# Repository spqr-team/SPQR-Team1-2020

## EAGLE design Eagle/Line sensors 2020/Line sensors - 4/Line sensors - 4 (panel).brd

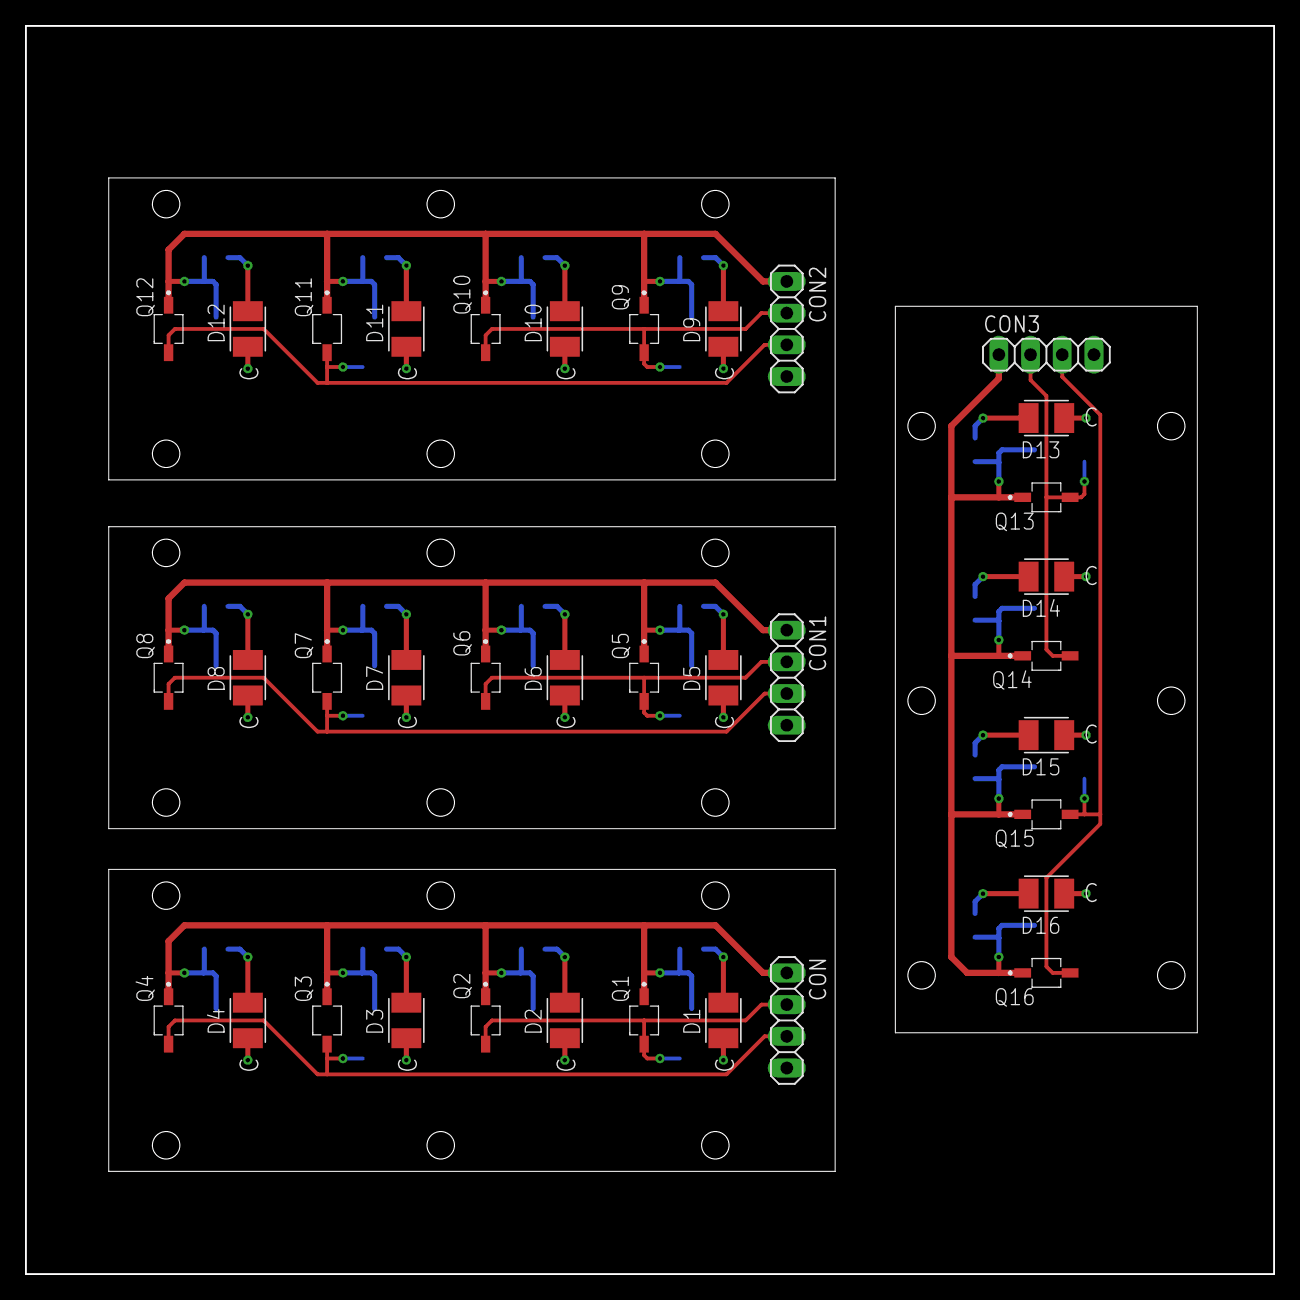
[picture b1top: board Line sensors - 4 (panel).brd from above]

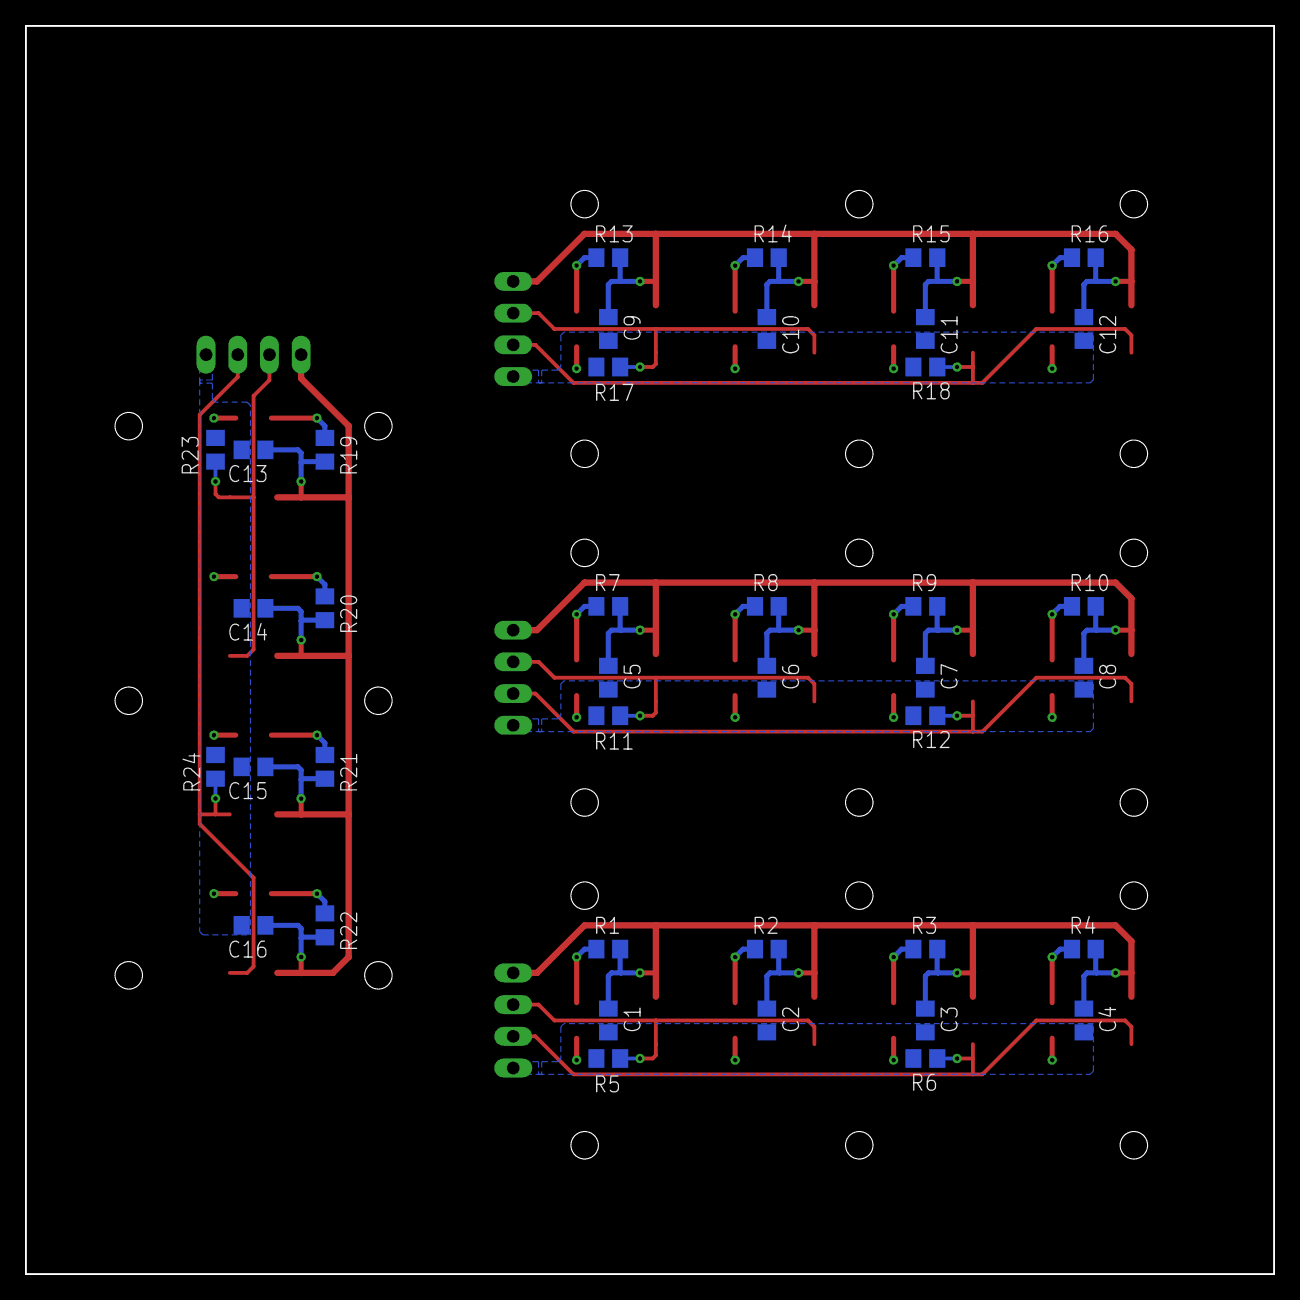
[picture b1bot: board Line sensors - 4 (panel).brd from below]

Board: 2 copper layers, 100.0 x 100.0 mm, 76 parts (40 on the bottom side), 32 nets.

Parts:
C1, C2, C3, C4, C5, C6, C7, C8, C9, C10, C11, C12, C13, C14, C15, C16: C0805
CON, CON1, CON2, CON3: 1X04
D1, D2, D3, D4, D5, D6, D7, D8, D9, D10, D11, D12, D13, D14, D15, D16: 3528-2PIN
Q1, Q2, Q3, Q4, Q5, Q6, Q7, Q8, Q9, Q10, Q11, Q12, Q13, Q14, Q15, Q16: VEMT2520X01
R1, R2, R3, R4, R5, R6, R7, R8, R9, R10, R11, R12, R13, R14, R15, R16, R17, R18, R19, R20, R21, R22, R23, R24: R0805

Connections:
GND: C1.2, C2.2, C3.2, C4.2, CON.4, D1.1, D2.1, D3.1, D4.1, R5.1, R6.1
GND1: C5.2, C6.2, C7.2, C8.2, CON1.4, D5.1, D6.1, D7.1, D8.1, R11.1, R12.1
GND2: C9.2, C10.2, C11.2, C12.2, CON2.4, D9.1, D10.1, D11.1, D12.1, R17.1, R18.1
GND3: C13.2, C14.2, C15.2, C16.2, CON3.4, D13.1, D14.1, D15.1, D16.1, R23.1, R24.1
unnamed: D1.2, R1.1
unnamed: D2.2, R2.1
unnamed: D3.2, R3.1
unnamed: D4.2, R4.1
unnamed: D5.2, R7.1
unnamed: D6.2, R8.1
unnamed: D7.2, R9.1
unnamed: D8.2, R10.1
unnamed: D9.2, R13.1
unnamed: D10.2, R14.1
unnamed: D11.2, R15.1
unnamed: D12.2, R16.1
unnamed: D13.2, R19.1
unnamed: D14.2, R20.1
unnamed: D15.2, R21.1
unnamed: D16.2, R22.1
SIG1: CON.2, Q1.2, Q2.2, R5.2
SIG2: CON.3, Q3.2, Q4.2, R6.2
SIG3: CON1.2, Q5.2, Q6.2, R11.2
SIG4: CON1.3, Q7.2, Q8.2, R12.2
SIG5: CON2.2, Q9.2, Q10.2, R17.2
SIG6: CON2.3, Q11.2, Q12.2, R18.2
SIG7: CON3.2, Q13.2, Q14.2, R23.2
SIG8: CON3.3, Q15.2, Q16.2, R24.2
V+: C1.1, C2.1, C3.1, C4.1, CON.1, Q1.1, Q2.1, Q3.1, Q4.1, R1.2, R2.2, R3.2, R4.2
V+1: C5.1, C6.1, C7.1, C8.1, CON1.1, Q5.1, Q6.1, Q7.1, Q8.1, R7.2, R8.2, R9.2, R10.2
V+2: C9.1, C10.1, C11.1, C12.1, CON2.1, Q9.1, Q10.1, Q11.1, Q12.1, R13.2, R14.2, R15.2, R16.2
V+3: C13.1, C14.1, C15.1, C16.1, CON3.1, Q13.1, Q14.1, Q15.1, Q16.1, R19.2, R20.2, R21.2, R22.2

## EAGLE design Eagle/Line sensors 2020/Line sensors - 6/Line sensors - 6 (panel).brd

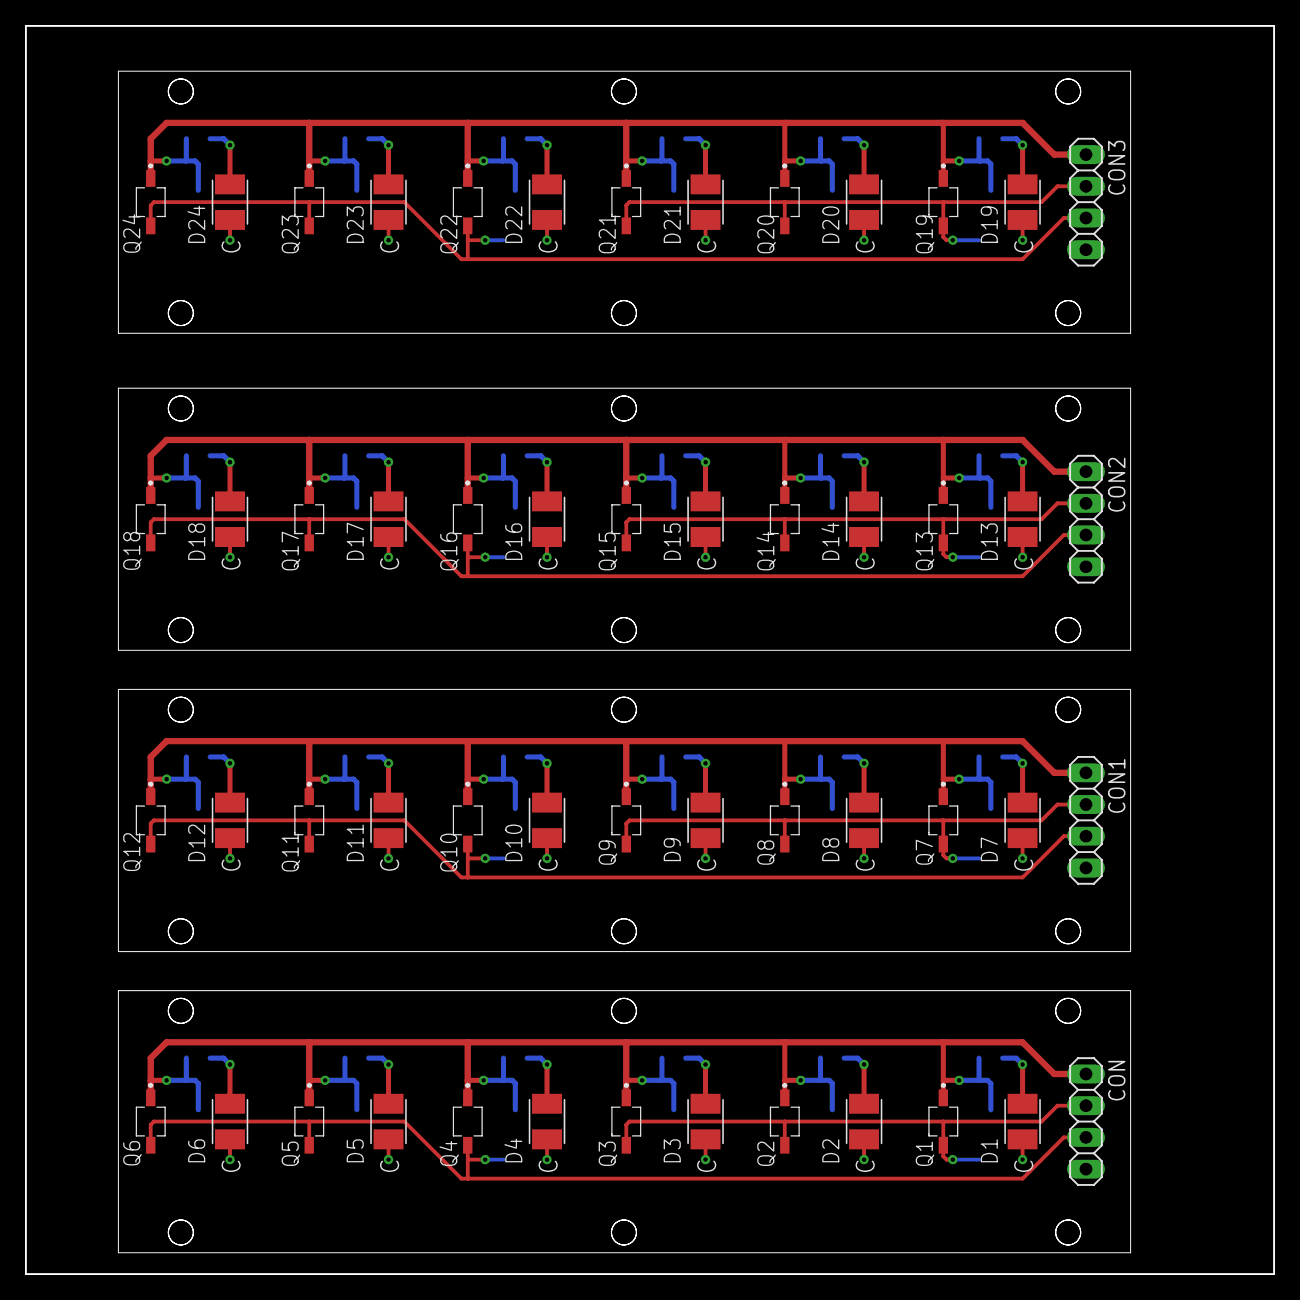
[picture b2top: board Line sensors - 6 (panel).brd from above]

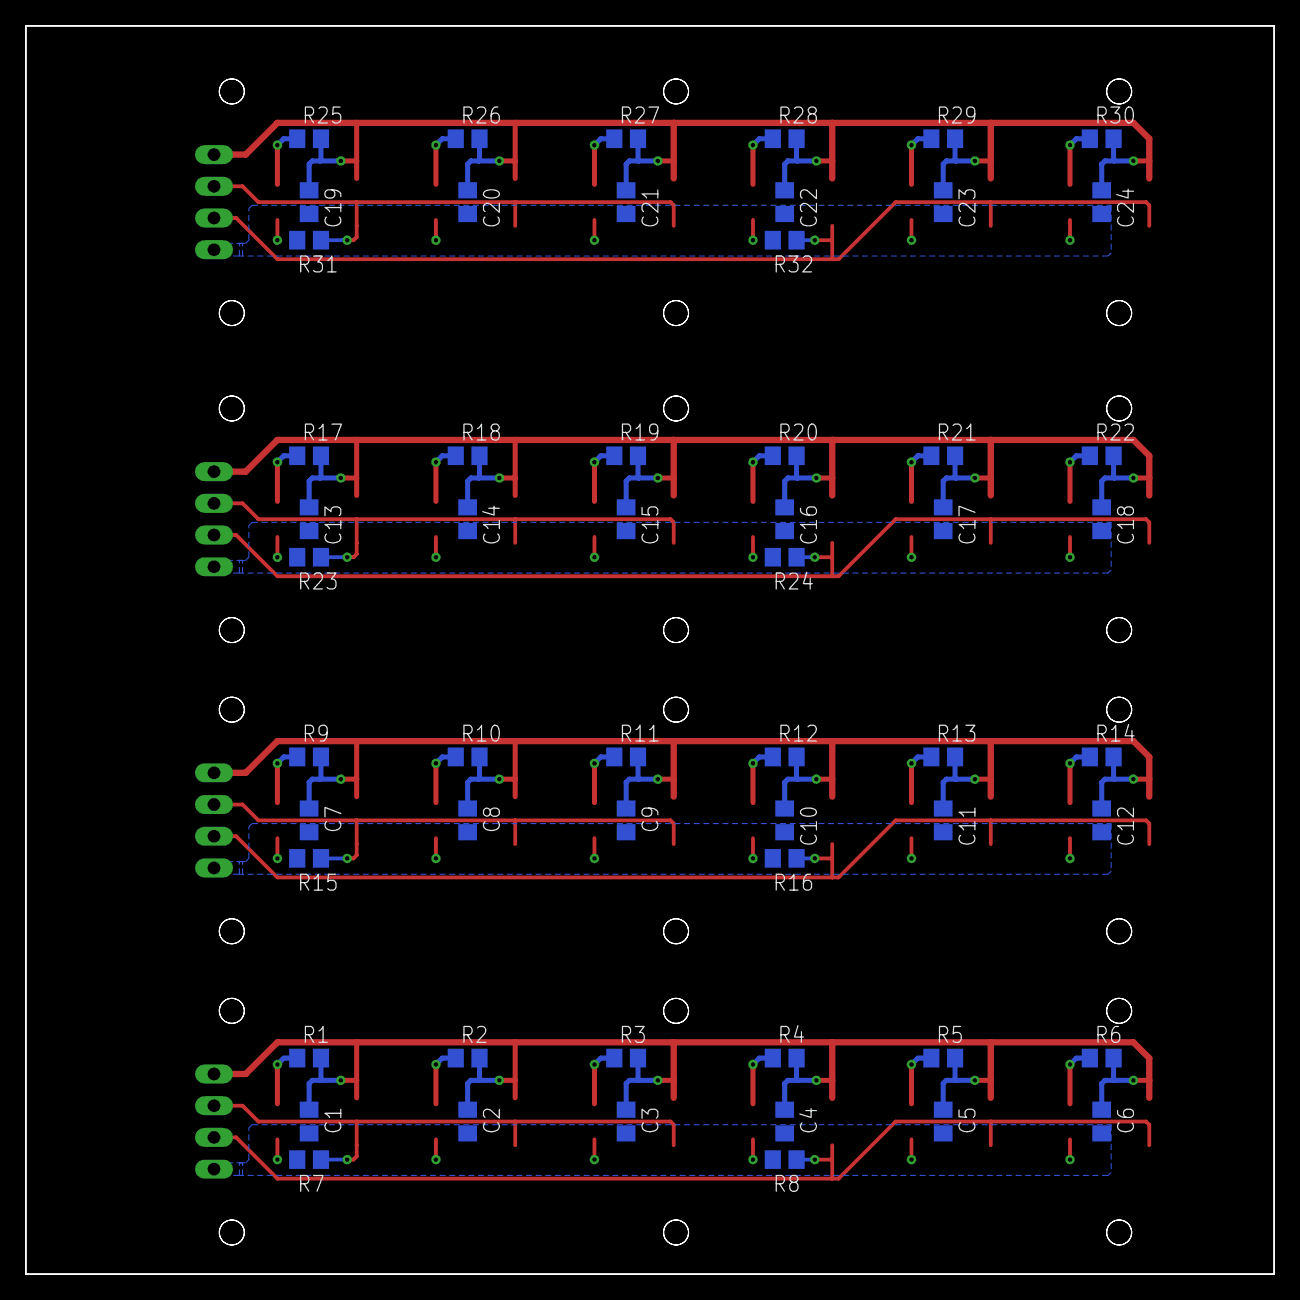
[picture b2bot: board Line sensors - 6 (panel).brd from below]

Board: 2 copper layers, 100.0 x 100.0 mm, 108 parts (56 on the bottom side), 40 nets.

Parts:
C1, C2, C3, C4, C5, C6, C7, C8, C9, C10, C11, C12, C13, C14, C15, C16, C17, C18, C19, C20, C21, C22, C23, C24: C0805
CON, CON1, CON2, CON3: 1X04
D1, D2, D3, D4, D5, D6, D7, D8, D9, D10, D11, D12, D13, D14, D15, D16, D17, D18, D19, D20, D21, D22, D23, D24: 3528-2PIN
Q1, Q2, Q3, Q4, Q5, Q6, Q7, Q8, Q9, Q10, Q11, Q12, Q13, Q14, Q15, Q16, Q17, Q18, Q19, Q20, Q21, Q22, Q23, Q24: VEMT2520X01
R1, R2, R3, R4, R5, R6, R7, R8, R9, R10, R11, R12, R13, R14, R15, R16, R17, R18, R19, R20, R21, R22, R23, R24, R25, R26, R27, R28, R29, R30, R31, R32: R0805

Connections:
GND: C1.2, C2.2, C3.2, C4.2, C5.2, C6.2, CON.4, D1.1, D2.1, D3.1, D4.1, D5.1, D6.1, R7.1, R8.1
GND1: C7.2, C8.2, C9.2, C10.2, C11.2, C12.2, CON1.4, D7.1, D8.1, D9.1, D10.1, D11.1, D12.1, R15.1, R16.1
GND2: C13.2, C14.2, C15.2, C16.2, C17.2, C18.2, CON2.4, D13.1, D14.1, D15.1, D16.1, D17.1, D18.1, R23.1, R24.1
GND3: C19.2, C20.2, C21.2, C22.2, C23.2, C24.2, CON3.4, D19.1, D20.1, D21.1, D22.1, D23.1, D24.1, R31.1, R32.1
unnamed: D1.2, R1.1
unnamed: D2.2, R2.1
unnamed: D3.2, R3.1
unnamed: D4.2, R4.1
unnamed: D5.2, R5.1
unnamed: D6.2, R6.1
unnamed: D7.2, R9.1
unnamed: D8.2, R10.1
unnamed: D9.2, R11.1
unnamed: D10.2, R12.1
unnamed: D11.2, R13.1
unnamed: D12.2, R14.1
unnamed: D13.2, R17.1
unnamed: D14.2, R18.1
unnamed: D15.2, R19.1
unnamed: D16.2, R20.1
unnamed: D17.2, R21.1
unnamed: D18.2, R22.1
unnamed: D19.2, R25.1
unnamed: D20.2, R26.1
unnamed: D21.2, R27.1
unnamed: D22.2, R28.1
unnamed: D23.2, R29.1
unnamed: D24.2, R30.1
SIG1: CON.2, Q1.2, Q2.2, Q3.2, R7.2
SIG2: CON.3, Q4.2, Q5.2, Q6.2, R8.2
SIG3: CON1.2, Q7.2, Q8.2, Q9.2, R15.2
SIG4: CON1.3, Q10.2, Q11.2, Q12.2, R16.2
SIG5: CON2.2, Q13.2, Q14.2, Q15.2, R23.2
SIG6: CON2.3, Q16.2, Q17.2, Q18.2, R24.2
SIG7: CON3.2, Q19.2, Q20.2, Q21.2, R31.2
SIG8: CON3.3, Q22.2, Q23.2, Q24.2, R32.2
V+: C1.1, C2.1, C3.1, C4.1, C5.1, C6.1, CON.1, Q1.1, Q2.1, Q3.1, Q4.1, Q5.1, Q6.1, R1.2, R2.2, R3.2, R4.2, R5.2, R6.2
V+1: C7.1, C8.1, C9.1, C10.1, C11.1, C12.1, CON1.1, Q7.1, Q8.1, Q9.1, Q10.1, Q11.1, Q12.1, R9.2, R10.2, R11.2, R12.2, R13.2, R14.2
V+2: C13.1, C14.1, C15.1, C16.1, C17.1, C18.1, CON2.1, Q13.1, Q14.1, Q15.1, Q16.1, Q17.1, Q18.1, R17.2, R18.2, R19.2, R20.2, R21.2, R22.2
V+3: C19.1, C20.1, C21.1, C22.1, C23.1, C24.1, CON3.1, Q19.1, Q20.1, Q21.1, Q22.1, Q23.1, Q24.1, R25.2, R26.2, R27.2, R28.2, R29.2, R30.2

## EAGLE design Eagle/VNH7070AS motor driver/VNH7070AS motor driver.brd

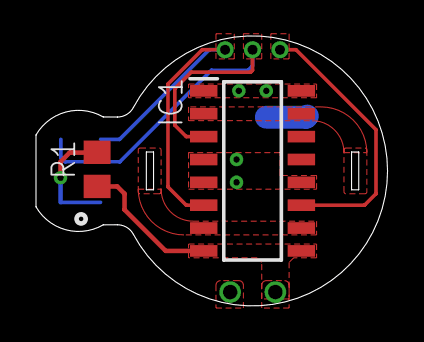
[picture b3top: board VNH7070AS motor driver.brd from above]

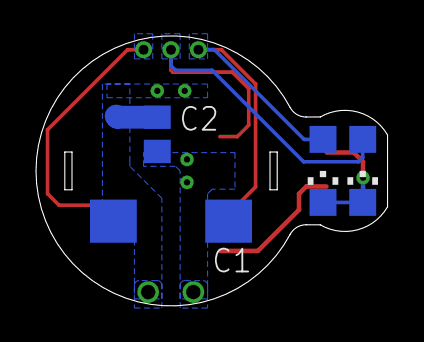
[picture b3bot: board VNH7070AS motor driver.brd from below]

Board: 2 copper layers, 19.5 x 15.0 mm, 6 parts (4 on the bottom side), 7 nets.

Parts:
C1: CT7343
C2: C0805
IC1: VNH7070ASTR; SOIC127P600X175-16N
LED1, LED2: CHIPLED_1206
R1: R0805

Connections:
+12V: C1.+, C2.1, IC1.4, IC1.5, IC1.12
GND: C1.-, C2.2, IC1.1, IC1.8, IC1.9, IC1.16, R1.1
IN_A: IC1.3, LED1.A
IN_B: IC1.6, LED2.A
unnamed: LED1.C, LED2.C, R1.2
V+: IC1.2, IC1.15
V-: IC1.7, IC1.10

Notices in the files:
parts and their libraries:
Wurth_Elektronik_Optoelectronics_rev15b: Copyright: Würth Elektronik
